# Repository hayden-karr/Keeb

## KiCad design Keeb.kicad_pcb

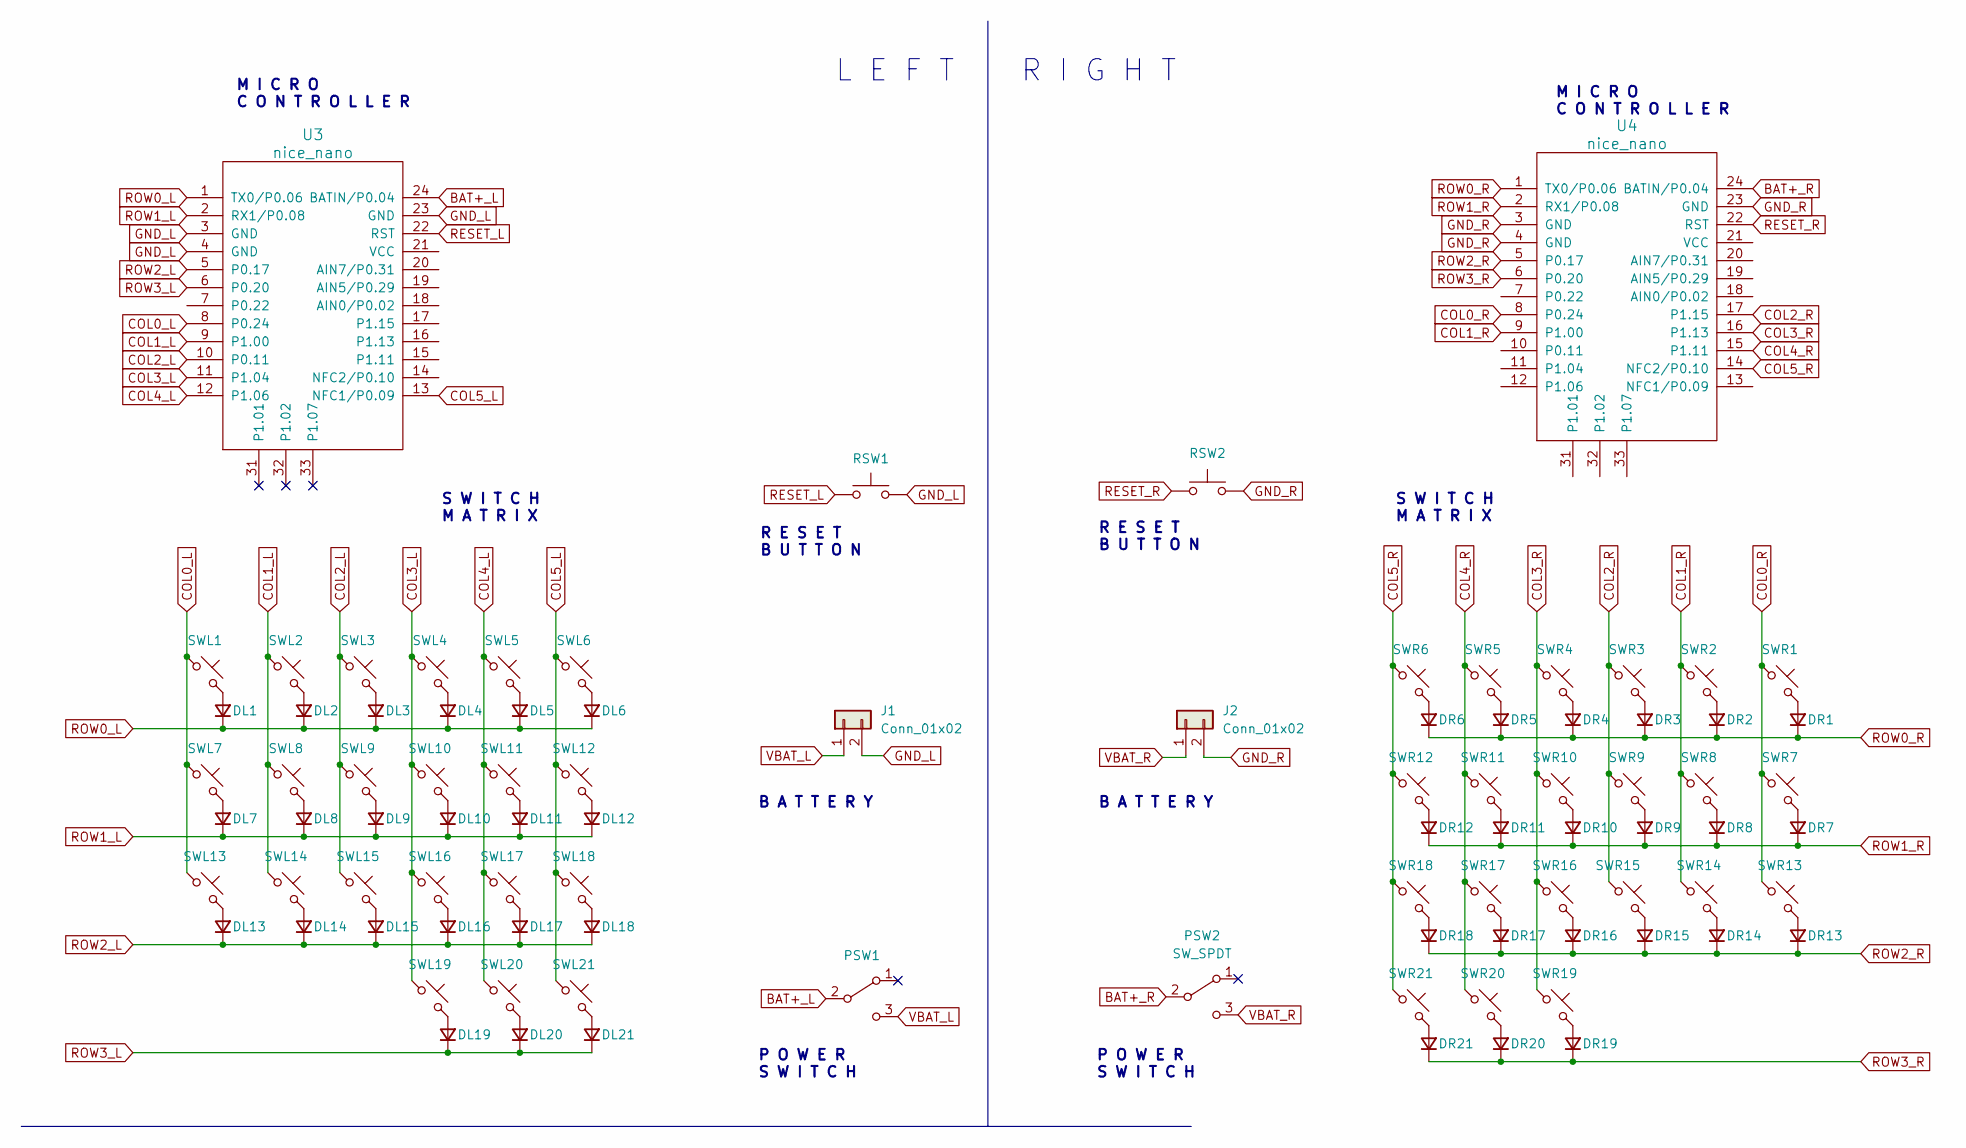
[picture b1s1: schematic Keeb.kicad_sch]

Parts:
DL1, DL2, DL3, DL4, DL5, DL6, DL7, DL8, DL9, DL10, DL11, DL12, DL13, DL14, DL15, DL16, DL17, DL18, DL19, DL20, DL21: D_Small; Diode_SOD123
DR1, DR2, DR3, DR4, DR5, DR6, DR7, DR8, DR9, DR10, DR11, DR12, DR13, DR14, DR15, DR16, DR17, DR18, DR19, DR20, DR21: D_Small; Diode_SOD123
J1, J2: Conn_01x02; JST-PH-2-SMT-RA
PSW1, PSW2: SW_SPDT; MSK12C02
RSW1, RSW2: SW_Push; SKHLLCA010
SWL1, SWL2, SWL3, SWL4, SWL5, SWL6, SWL7, SWL8, SWL9, SWL10, SWL11, SWL12, SWL13, SWL14, SWL15, SWL16, SWL17, SWL18, SWL19, SWL20, SWL21: SW_Push_45deg; MX-Hotswap-1U
SWR1, SWR2, SWR3, SWR4, SWR5, SWR6, SWR7, SWR8, SWR9, SWR10, SWR11, SWR12, SWR13, SWR14, SWR15, SWR16, SWR17, SWR18, SWR19, SWR20, SWR21: SW_Push_45deg; MX-Hotswap-1U
U3, U4: nice_nano

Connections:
BAT+_L: PSW1.2 (B), U3.24 (BATIN/P0.04)
BAT+_R: PSW2.2 (B), U4.24 (BATIN/P0.04)
COL0_L: SWL1.1, SWL7.1, SWL13.1, U3.8 (P0.24)
COL0_R: SWR1.1, SWR7.1, SWR13.1, U4.8 (P0.24)
COL1_L: SWL2.1, SWL8.1, SWL14.1, U3.9 (P1.00)
COL1_R: SWR2.1, SWR8.1, SWR14.1, U4.9 (P1.00)
COL2_L: SWL3.1, SWL9.1, SWL15.1, U3.10 (P0.11)
COL2_R: SWR3.1, SWR9.1, SWR15.1, U4.17 (P1.15)
COL3_L: SWL4.1, SWL10.1, SWL16.1, SWL19.1, U3.11 (P1.04)
COL3_R: SWR4.1, SWR10.1, SWR16.1, SWR19.1, U4.16 (P1.13)
COL4_L: SWL5.1, SWL11.1, SWL17.1, SWL20.1, U3.12 (P1.06)
COL4_R: SWR5.1, SWR11.1, SWR17.1, SWR20.1, U4.15 (P1.11)
COL5_L: SWL6.1, SWL12.1, SWL18.1, SWL21.1, U3.13 (NFC1/P0.09)
COL5_R: SWR6.1, SWR12.1, SWR18.1, SWR21.1, U4.14 (NFC2/P0.10)
GND_L: J1.2, RSW1.2, U3.3 (GND), U3.4 (GND), U3.23 (GND)
GND_R: J2.2, RSW2.2, U4.3 (GND), U4.4 (GND), U4.23 (GND)
unnamed: DL1.2 (A), SWL1.2
unnamed: DL2.2 (A), SWL2.2
unnamed: DL3.2 (A), SWL3.2
unnamed: DL4.2 (A), SWL4.2
unnamed: DL5.2 (A), SWL5.2
unnamed: DL6.2 (A), SWL6.2
unnamed: DL7.2 (A), SWL7.2
unnamed: DL8.2 (A), SWL8.2
unnamed: DL9.2 (A), SWL9.2
unnamed: DL10.2 (A), SWL10.2
unnamed: DL11.2 (A), SWL11.2
unnamed: DL12.2 (A), SWL12.2
unnamed: DL13.2 (A), SWL13.2
unnamed: DL14.2 (A), SWL14.2
unnamed: DL15.2 (A), SWL15.2
unnamed: DL16.2 (A), SWL16.2
unnamed: DL17.2 (A), SWL17.2
unnamed: DL18.2 (A), SWL18.2
unnamed: DL19.2 (A), SWL19.2
unnamed: DL20.2 (A), SWL20.2
unnamed: DL21.2 (A), SWL21.2
unnamed: DR1.2 (A), SWR1.2
unnamed: DR2.2 (A), SWR2.2
unnamed: DR3.2 (A), SWR3.2
unnamed: DR4.2 (A), SWR4.2
unnamed: DR5.2 (A), SWR5.2
unnamed: DR6.2 (A), SWR6.2
unnamed: DR7.2 (A), SWR7.2
unnamed: DR8.2 (A), SWR8.2
unnamed: DR9.2 (A), SWR9.2
unnamed: DR10.2 (A), SWR10.2
unnamed: DR11.2 (A), SWR11.2
unnamed: DR12.2 (A), SWR12.2
unnamed: DR13.2 (A), SWR13.2
unnamed: DR14.2 (A), SWR14.2
unnamed: DR15.2 (A), SWR15.2
unnamed: DR16.2 (A), SWR16.2
unnamed: DR17.2 (A), SWR17.2
unnamed: DR18.2 (A), SWR18.2
unnamed: DR19.2 (A), SWR19.2
unnamed: DR20.2 (A), SWR20.2
unnamed: DR21.2 (A), SWR21.2
RESET_L: RSW1.1, U3.22 (RST)
RESET_R: RSW2.1, U4.22 (RST)
ROW0_L: DL1.1 (K), DL2.1 (K), DL3.1 (K), DL4.1 (K), DL5.1 (K), DL6.1 (K), U3.1 (TX0/P0.06)
ROW0_R: DR1.1 (K), DR2.1 (K), DR3.1 (K), DR4.1 (K), DR5.1 (K), DR6.1 (K), U4.1 (TX0/P0.06)
ROW1_L: DL7.1 (K), DL8.1 (K), DL9.1 (K), DL10.1 (K), DL11.1 (K), DL12.1 (K), U3.2 (RX1/P0.08)
ROW1_R: DR7.1 (K), DR8.1 (K), DR9.1 (K), DR10.1 (K), DR11.1 (K), DR12.1 (K), U4.2 (RX1/P0.08)
ROW2_L: DL13.1 (K), DL14.1 (K), DL15.1 (K), DL16.1 (K), DL17.1 (K), DL18.1 (K), U3.5 (P0.17)
ROW2_R: DR13.1 (K), DR14.1 (K), DR15.1 (K), DR16.1 (K), DR17.1 (K), DR18.1 (K), U4.5 (P0.17)
ROW3_L: DL19.1 (K), DL20.1 (K), DL21.1 (K), U3.6 (P0.20)
ROW3_R: DR19.1 (K), DR20.1 (K), DR21.1 (K), U4.6 (P0.20)
VBAT_L: J1.1, PSW1.3 (C)
VBAT_R: J2.1, PSW2.3 (C)

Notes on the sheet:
R E S E T B U T T O N
P O W E R S W I T C H
B A T T E R Y
S W I T C H M A T R I X
M I C R O C O N T R O L L E R
L E F T
R I G H T

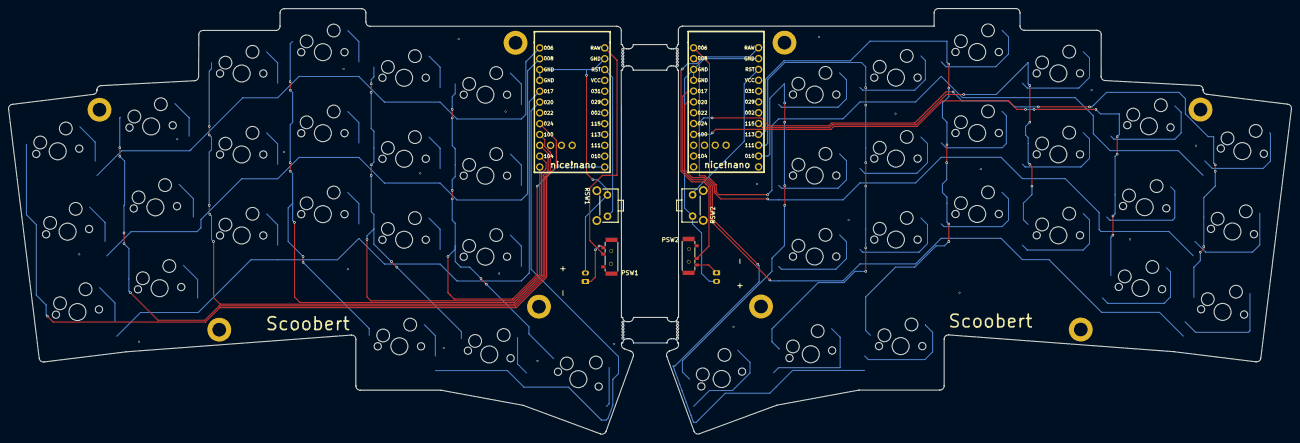
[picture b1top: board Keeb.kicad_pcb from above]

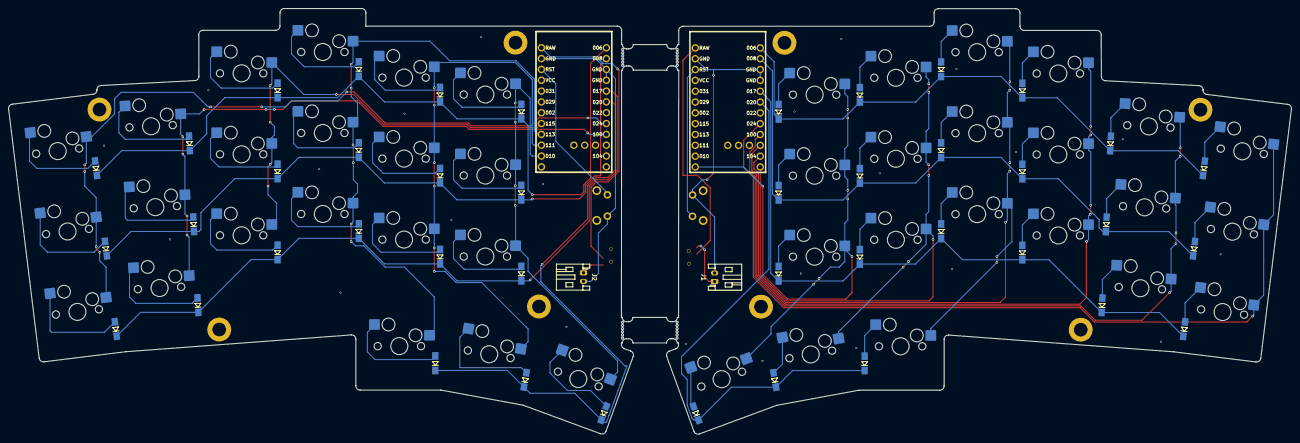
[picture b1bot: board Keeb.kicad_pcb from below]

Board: 2 copper layers, 301.0 x 99.8 mm, 92 parts (86 on the bottom side), 70 nets.

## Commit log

2025-06-23 Init
2025-06-24 Readme + Image
2025-06-24 Readme image
